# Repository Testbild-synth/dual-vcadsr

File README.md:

# Eurorack DUAL Voltage controlled AR / ADSR / LFO / Random / S&H Utility Module

This project is a dual utility module on the basis of an Arduino nano that does a bunch of neat things.
It is fully through hole and has relatively standard parts (safe for maybe the DAC module but you can get that on aliexpress)

## Status
Has been built by multiple people and works fine! 
I have gotten complaints about small holes for the pushbuttons so I created a V1.1 with 
bigger holes in the PCB and the panel to allow a wider variety of pushbutton parts.

## Hardware and PCB

The module has one Panel PCB and one circuit PCB, relatively straight forward, just order with standard settings on jlcpcb or any other pcb site.
The build is relatively straight forward, but there is one spot at the top where the IC and pot kind of overlap a bit. be sure
to not have stuff standing out too much from the IC so that it contacts the metal housing of the pots and shorts. should be doable

## Status
Has been built by multiple people and works fine! 
I have gotten complaints about small holes for the pushbuttons so I created a V1.1 with 
bigger holes in the PCB and the panel to allow a wider variety of pushbutton parts.

## Code

The code is under the firmware folder and can be uploaded to the nano using the arduino IDE.
For the MUX chip it uses the "Analog digital Multiplexers" library found here: [source repo](https://github.com/stechio/arduino-ad-mux-lib?tab=readme-ov-file) ,
[arduino libraries page](https://docs.arduino.cc/libraries/analog-digital-multiplexers/).
You can get it from the library browser inside arduino IDE.

## Operation
In general, to make it easier on myself I have wired it such that the CV replaces knob values so the knobs are useless if something is plugged in.
In my experience this is not that much of a problem as you usually either want to dial in a specific shape or have an lfo etc plugged in.
The cool (at least I think it's cool) thing is that you can change CV during a phase to affect the progession of the current phase.

The modules has the following modes:
 - Attack-release: When triggered, does an attack, then a release
 - Attack-Decay-sustain-release: When triggered, does ADSR as a normal envelope would. 
 - Long Attack-Decay-sustain-release: as normal ADSR but longer by a factor 10
 - LFO: Goes from Attack to Decay to release immediately, then back to attack. Trigger retriggers the attack stage
 - RAND: Random values. Attack Pot changes minimum value, Decay pot changes value range. Each trigger gives a new value. **By plugging in CV to attack and setting Decay pot to 0 you can use it as a sample/hold which I think is very neat!** Sustain pot quantizes to one of six scales, but this is a bit experimental and might now work perfectly since all output is scaled by the scale pot and by arduino internal 5V conversion anyways.

 Curve switch switches between linear, exponential and logarithmic. This is the one thing shared by both channels otherwise they operate independently.

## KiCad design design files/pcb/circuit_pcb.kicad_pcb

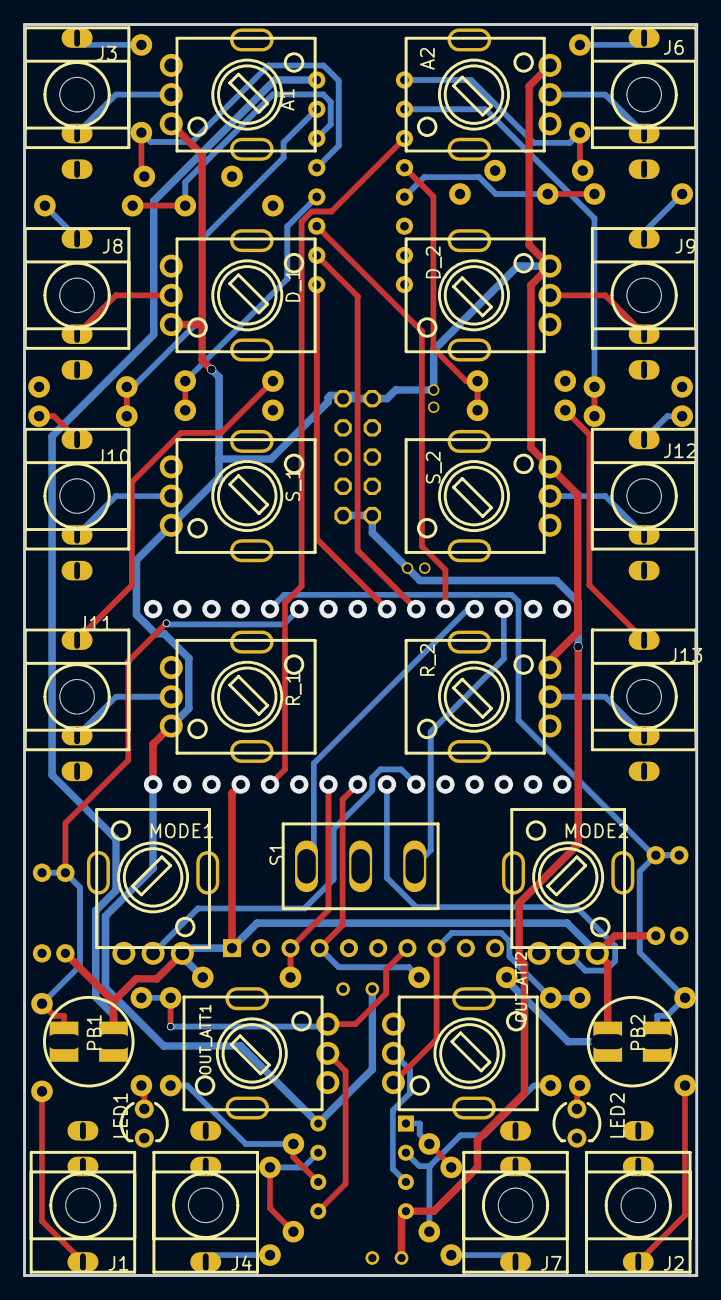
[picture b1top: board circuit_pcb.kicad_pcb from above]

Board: 2 copper layers, 58.4 x 108.7 mm, 69 parts (0 on the bottom side), 46 nets.

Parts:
A1, A2: 100k; R09-5KΩ
C1, C2: 10u; CAP-D4.0×F1.5
C3, C4: 100n; RAD-0.1
D1, D2, D3, D4: S; DO-34_BD1.6-L3.0-P7.00-D0.6-RD
D_1, D_2: 100k; R09-5KΩ
EP1: PWER; EURORACK_POWER_V2
J1: TRIG1_IN; THONKICONN_1
J2: TRIG2_IN; THONKICONN_1
J3: CVA1; THONKICONN_1
J4: OUT_1; THONKICONN_1
J5: MCP4728; HDR-M-2.54_1X10
J6: CVA2; THONKICONN_1
J7: OUT_2; THONKICONN_1
J8: CVD1; THONKICONN_1
J9: CVD2; THONKICONN_1
J10: CVS1; THONKICONN_1
J11: CVR1; THONKICONN_1
J12: CVS2; THONKICONN_1
J13: CVR2; THONKICONN_1
LED1, LED2: LED TBR; LED-3MM/2.54
MODE1, MODE2: 100k; R09-5KΩ
OUT_ATT1, OUT_ATT2: 100k; R09-5KΩ
PB1: TRIG1; PUSHBUTTON
PB2: TRIG2; PUSHBUTTON
R1, R2, R4, R13: 1k; R_AXIAL-0.3
R3, R11: 200k; R_AXIAL-0.3
R5, R15: 100k; R_AXIAL-0.3
R6, R12, R17, R19, R21, R22, R25, R26: 47k; R_AXIAL-0.3
R7, R16: 10k; R_AXIAL-0.3
R8, R10: 3k3; R_AXIAL-0.3
R9, R14, R18, R20, R23, R24, R27, R28: 33k; R_AXIAL-0.3
R_1, R_2: 100k; R09-5KΩ
S1: SPDT; TOGGLE SWITCH SPDT RED 3 PIN ON-OFF-ON 3 SPDT SMALL AC 6A/1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
S_1, S_2: 100k; R09-5KΩ
U1: CD74HC4051_THT_DIP-16
U3: TL072; DIP8

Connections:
12V: A1.3, A2.3, C2.1, C3.1, D_1.3, D_2.3, EP1.12, R_1.3, R_2.3, S_1.3, S_2.3, U3.8
-12V: C1.2, C4.1, EP1.-12, U3.4
A2_2: A2.2, J6.2
ARD_5: D1.1, D3.1, J5.1, MODE1.3, MODE2.3, PB1.2, PB2.2, R8.1, R10.1, U1.16
ATK1: R6.1, R9.2, U1.13
ATK2: R12.1, R14.2, U1.1
DEC1: R17.1, R18.2, U1.14
DEC2: R19.1, R20.2, U1.5
GND: A1.1, A2.1, C1.1, C2.2, C3.2, C4.2, D2.2, D4.2, D_1.1, D_2.1, EP1.GND0, EP1.GND1, EP1.GND2, EP1.GND3, EP1.GND4, EP1.GND5, J1.1, J1.2, J2.1, J2.2, J3.1, J4.1, J5.2, J5.5, J6.1, J7.1, J8.1, J9.1, J10.1, J11.1, J12.1, J13.1, LED1.2, LED2.2, MODE1.1, MODE2.1, OUT_ATT1.1, OUT_ATT2.1, R9.1, R14.1, R18.1, R20.1, R23.1, R24.1, R27.1, R28.1, R_1.1, R_2.1, S1.2, S_1.1, S_2.1, U1.6, U1.7, U1.8
J3_2: A1.2, J3.2
J6_3: J6.3, R12.2
J7_3: J7.3, R13.1
J8_2: D_1.2, J8.2
J9_2: D_2.2, J9.2
J10_2: J10.2, S_1.2
J11_3: J11.3, R22.2
J12_3: J12.3, R25.2
J13_2: J13.2, R_2.2
LED1_1: LED1.1, R7.2
O_1: J5.7, OUT_ATT1.3, R5.2, R7.1
O_2: J5.8, OUT_ATT2.3, R15.2, R16.1
R1_2: J1.3, R1.2
R2_2: J2.3, R2.2
R4_1: J4.3, R4.1
R6_2: J3.3, R6.2
R16_2: LED2.1, R16.2
R17_2: J8.3, R17.2
R19_2: J9.3, R19.2
R21_2: J10.3, R21.2
R26_2: J13.3, R26.2
REL1: R22.1, R24.2, U1.12
REL2: R26.1, R28.2, U1.4
R_1_2: J11.2, R_1.2
SCL: J5.3, R8.2
SDA: J5.4, R10.2
SUS1: R21.1, R23.2, U1.15
SUS2: R25.1, R27.2, U1.2
S_2_2: J12.2, S_2.2
TRIG_1: D1.2, D2.1, PB1.1, R1.1
TRIG_2: D3.2, D4.1, PB2.1, R2.1
U3_1: R11.1, R13.2, U3.1
U3_2: R11.2, R15.1, U3.2
U3_3: OUT_ATT2.2, U3.3
U3_5: OUT_ATT1.2, U3.5
U3_6: R3.2, R5.1, U3.6
U3_7: R3.1, R4.2, U3.7

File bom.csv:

ID,Name,Designator,Footprint,Quantity,
1,100k Potentiometer,"A1,A2,D_1,D_2,MODE1,MODE2,R_1,R_2,S_1,S_2,OUT_ATT1,OUT_ATT2",R09k potentiometer,12,
2,Eurorack jacks Thonkiconn,,Eurorack jack Thonkiconn,12,
14,LED TBR,"LED1,LED2",LED-3MM/2.54,2,
15,TRIG1,"PB1, PB2",Pushbutton NORMALLY OPEN 6mm ,1,like this footprint but NO version https://makerselectronics.com/product/round-momentary-push-b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
17,SPDT,S1,TOGGLE SWITCH SPDT RED 3 PIN ON-OFF-ON 3 SPDT SMALL AC 6A/125V 3A/250V,1,
18,10u,"C1,C2",CAP-D4.0×F1.5,2,
19,100n,"C3,C4",RAD-0.1,2,
20,Schottky diode (BAT43),"D1,D2,D3,D4",DO-34_BD1.6-L3.0-P7.00-D0.6-RD,4,
21,Power header,EP1,EURORACK_POWER_V2,1,
22,MCP4728,J5,this thing: https://eckstein-shop.de/GY-MCP472812BitDigitaltoAnalogConve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 or similar footprint,1,
23,1k,"R1,R2,R4,R13",R_AXIAL-0.3,4,
24,200k,"R3,R11",R_AXIAL-0.3,2,
25,100k,"R5,R15",R_AXIAL-0.3,2,
26,47k,"R6,R12,R17,R19,R21,R22,R25,R26",R_AXIAL-0.3,8,
27,10k,"R7,R16",R_AXIAL-0.3,2,
28,3k3,"R8,R10",R_AXIAL-0.3,2,
29,33k,"R9,R14,R18,R20,R23,R24,R27,R28",R_AXIAL-0.3,8,
30,CD74HC4051_THT_DIP-16,U1,CD74HC4051_THT_DIP-16,1,
31,TL072,U3,DIP8,1,

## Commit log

2024-12-10 initial file upload
2025-02-26 added comment about library to code and readme
2025-02-26 panel with bigger holes for pushbuttons
2025-02-26 V1.1 pcb (only changes are bigger switch holes and a nametag)
